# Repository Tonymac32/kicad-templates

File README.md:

# kicad-templates
Single Board Computer accessory templates for KiCad

---

This repository is for templates to make accessory boards or "hats" for single board computers. 

Currently supported:
- NanoPi NEO/NEO2/AIR/NEO Plus2

Partially Supported:
- NanoPi NEO Core (by NanoPi NEO)

As always, I enjoy contributing to the community.  If you like what I do and want to see more, [donate Here][paypal]

[paypal]: https://www.paypal.com/cgi-bin/webscr?cmd=_s-xclick&hosted_button_id=6JRRCSB28828Y&source=url

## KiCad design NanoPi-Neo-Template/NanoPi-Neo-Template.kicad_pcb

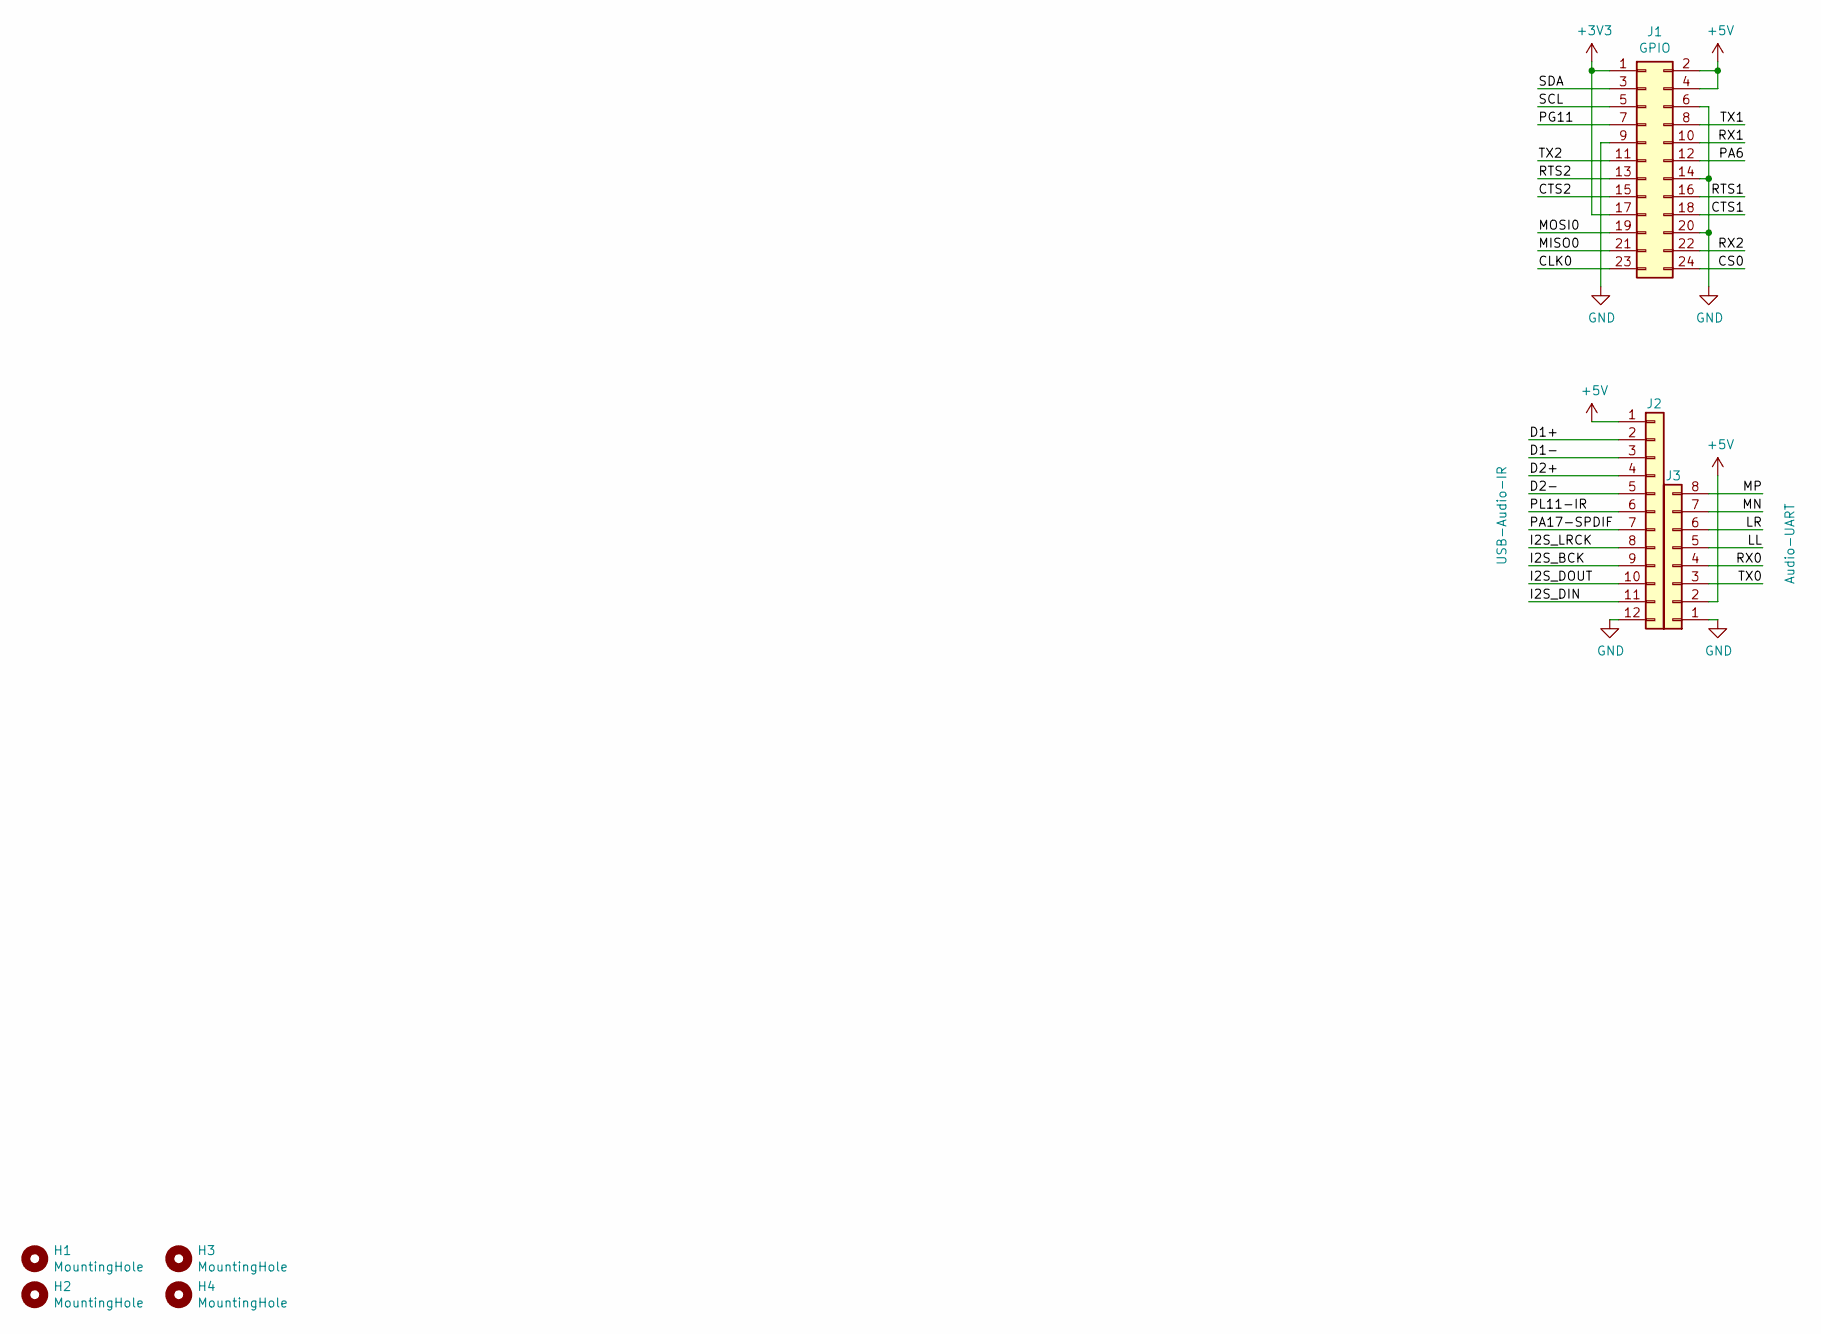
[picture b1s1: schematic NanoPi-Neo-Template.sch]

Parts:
H1, H2, H3, H4: MountingHole; MountingHole_3mm
J1: GPIO; Socket_Strip_Straight_2x12_Pitch2.54mm
J2: USB-Audio-IR; Socket_Strip_Straight_1x12_Pitch2.54mm
J3: Audio-UART; Socket_Strip_Straight_1x08_Pitch2.54mm

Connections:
+3V3: J1.1, J1.17
+5V: J1.2, J1.4, J2.1, J3.2
/CLK0: J1.23
/CS0: J1.24
/CTS1: J1.18
/CTS2: J1.15
/D1+: J2.2
/D1-: J2.3
/D2+: J2.4
/D2-: J2.5
/I2S_BCK: J2.9
/I2S_DIN: J2.11
/I2S_DOUT: J2.10
/I2S_LRCK: J2.8
/LL: J3.5
/LR: J3.6
/MISO0: J1.21
/MN: J3.7
/MOSI0: J1.19
/MP: J3.8
/PA6: J1.12
/PA17-SPDIF: J2.7
/PG11: J1.7
/PL11-IR: J2.6
/RTS1: J1.16
/RTS2: J1.13
/RX0: J3.4
/RX1: J1.10
/RX2: J1.22
/SCL: J1.5
/SDA: J1.3
/TX0: J3.3
/TX1: J1.8
/TX2: J1.11
GND: J1.6, J1.9, J1.14, J1.20, J2.12, J3.1

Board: 2 copper layers, 7 parts (3 on the bottom side), 3 nets, no tracks yet.

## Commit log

2019-02-28 Initial Commit
    This template applies to NanoPi NEO, NEO2, AIR, and works with NanoPi Neo CORE
2019-02-28 add docs folder
2019-02-28 add nanopi NEO shield image
2019-02-28 Add image for nanopi neo
    also fix a typo.
